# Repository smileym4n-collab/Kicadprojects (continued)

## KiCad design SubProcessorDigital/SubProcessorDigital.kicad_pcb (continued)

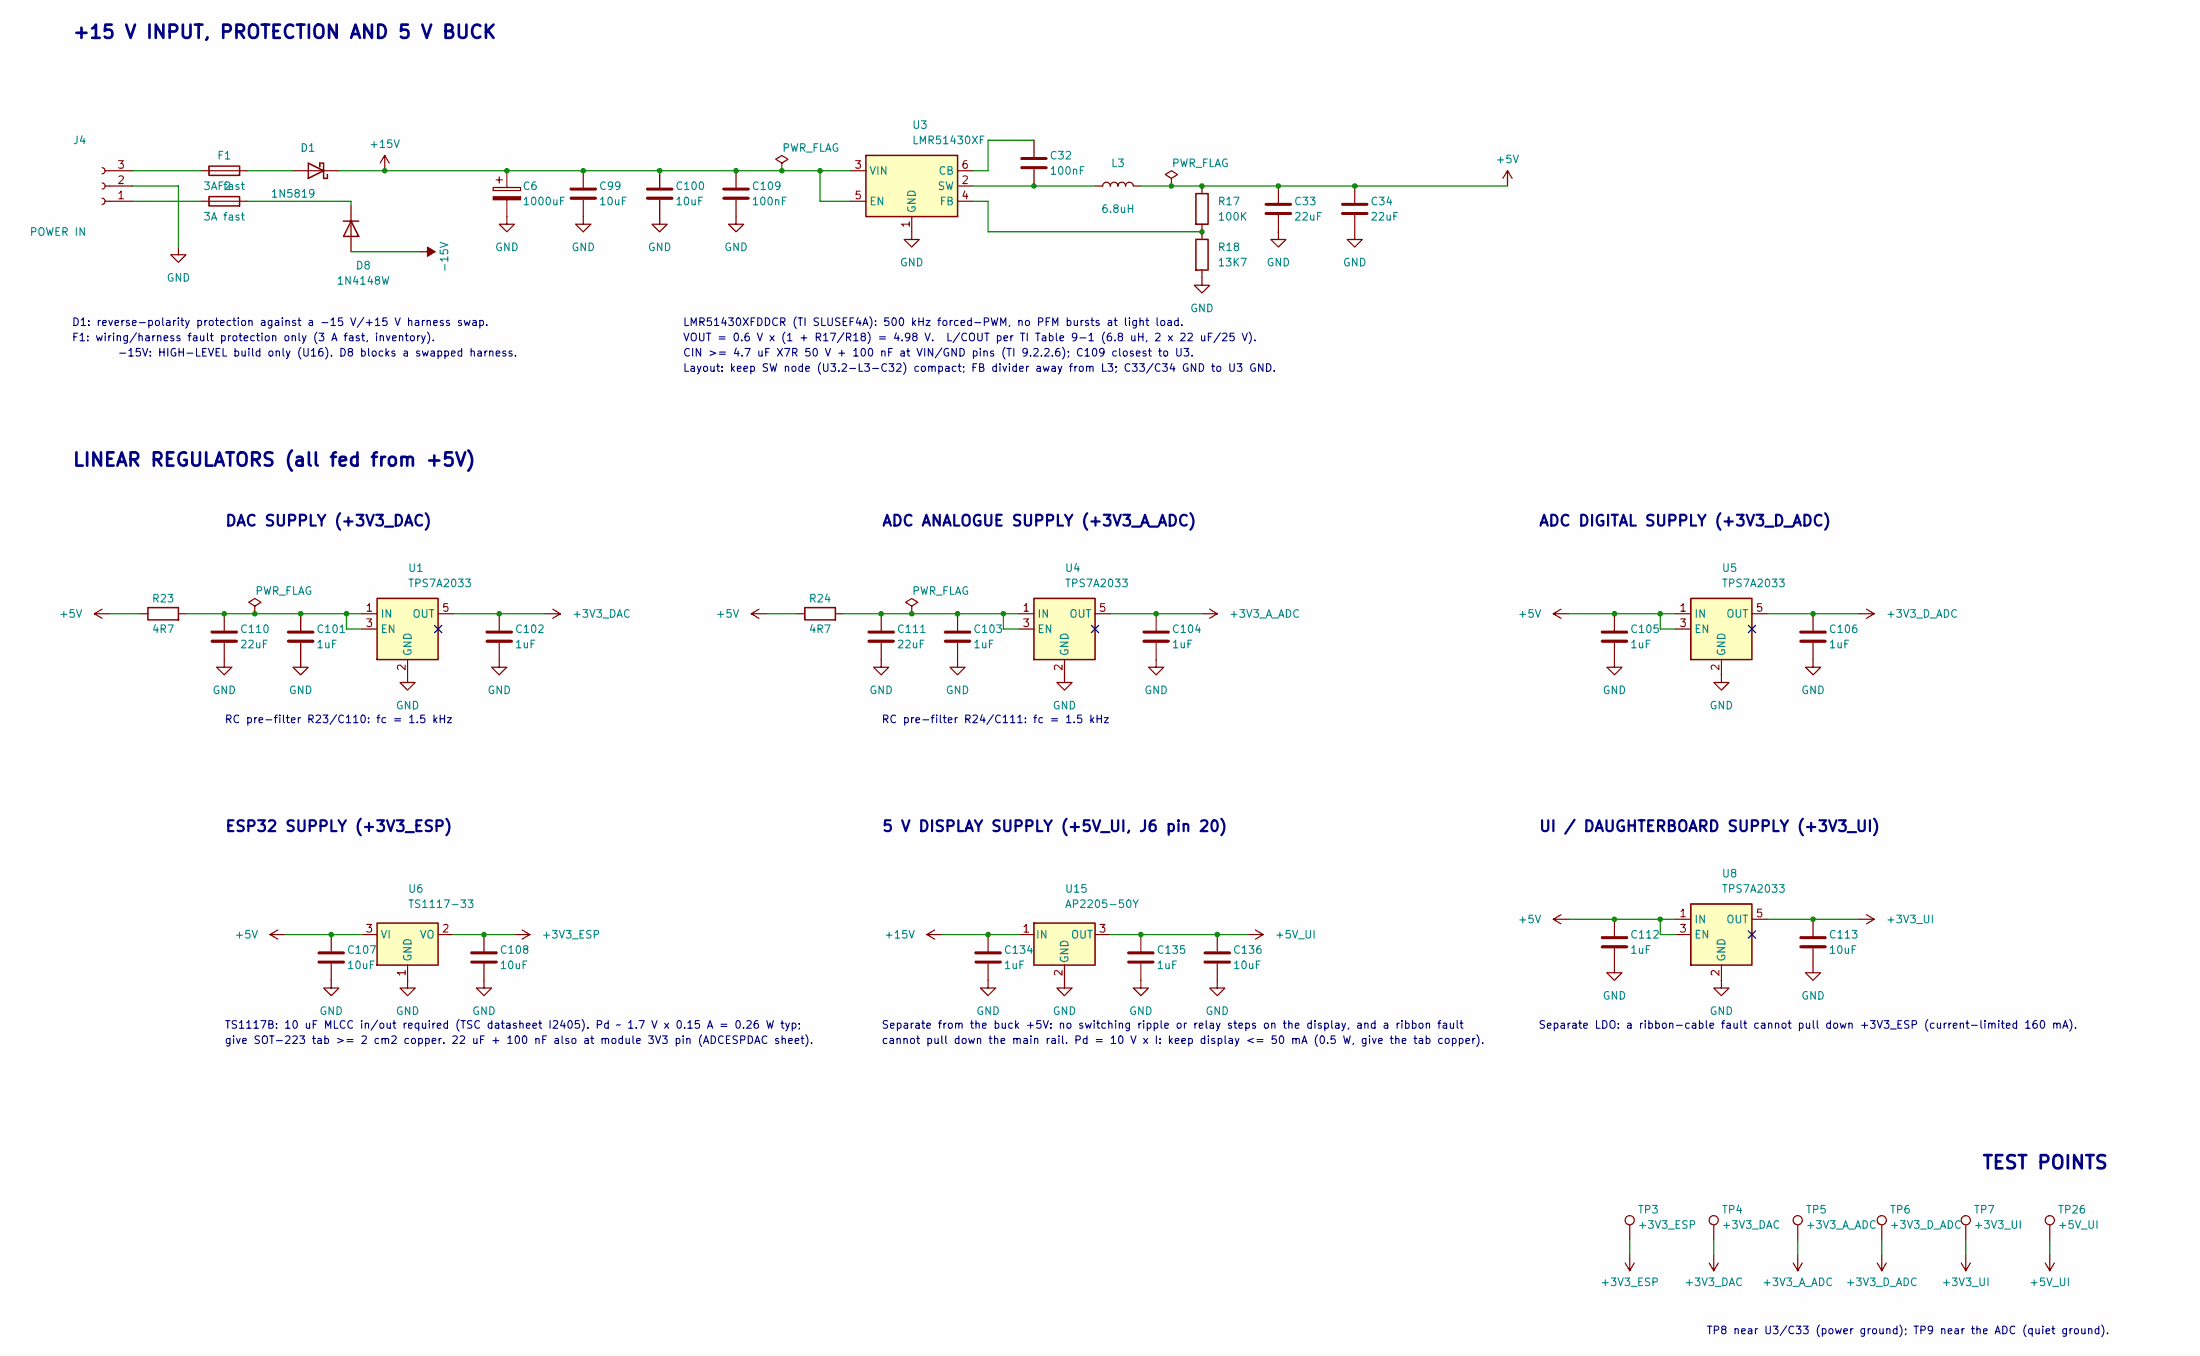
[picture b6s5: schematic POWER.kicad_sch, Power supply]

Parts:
C6: 1000uF; CP_Radial_D12.5mm_P5.00mm; MPN Panasonic EEUFR1V102 (FR)
C32, C109: 100nF; C_0603_1608Metric_Pad1.08x0.95mm_HandSolder; MPN Multicomp Pro MC0603B104K500CT (100nF 5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
C33, C34: 22uF; C_1206_3216Metric_Pad1.33x1.80mm_HandSolder; MPN Samsung CL31A226KAHNNNE X5R 25V 3216 (i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
C99, C100: 10uF; C_1206_3216Metric_Pad1.33x1.80mm_HandSolder; MPN Samsung CL31A106KBHNNNE (inventory)
C101, C102, C103, C104, C105, C106, C112: 1uF; C_1206_3216Metric_Pad1.33x1.80mm_HandSolder; MPN Samsung CL31B105KBHNFNE
C107, C108: 10uF; C_1206_3216Metric_Pad1.33x1.80mm_HandSolder; MPN Taiyo Yuden TMK316B7106KL-TD
C110, C111: 22uF; C_1206_3216Metric_Pad1.33x1.80mm_HandSolder; MPN Samsung CL31A226KAHNNNE (22uF 25V X5R 3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
C113: 10uF; C_0805_2012Metric_Pad1.18x1.45mm_HandSolder; MPN Samsung CL21A106KOQNNNF
C134, C135: 1uF; C_1206_3216Metric_Pad1.33x1.80mm_HandSolder; MPN Samsung CL31B105KBHNFNE (inventory)
C136: 10uF; C_0805_2012Metric_Pad1.18x1.45mm_HandSolder; MPN Samsung CL21A106KOQNNNF (inventory)
D1: 1N5819; D_DO-41_SOD81_P10.16mm_Horizontal; MPN Diotec 1N5819
D8: 1N4148W; D_SOD-123; MPN onsemi 1N4148W (inventory)
F1, F2: 3A fast; Fuse_1206_3216Metric_Pad1.42x1.75mm_HandSolder; MPN Bel Fuse C1F 3
J4: POWER IN; JST_XH_B3B-XH-A_1x03_P2.50mm_Vertical; MPN JST B3B-XH-A
L3: 6.8uH; SRP6030WA-6R8M; MPN Bourns SRP6030WA-6R8M (inventory)
R17: 100K; R_0805_2012Metric_Pad1.20x1.40mm_HandSolder; MPN 100k thin film 0.5% 2012 (inventory)
R18: 13K7; R_0805_2012Metric_Pad1.20x1.40mm_HandSolder; MPN 13k7 thick film 1% 2012 (inventory)
R23, R24: 4R7; R_0805_2012Metric_Pad1.20x1.40mm_HandSolder; MPN 4R7 thick film 2012 (inventory)
TP3: +3V3_ESP; TestPoint_Pad_D1.5mm
TP4: +3V3_DAC; TestPoint_Pad_D1.5mm
TP5: +3V3_A_ADC; TestPoint_Pad_D1.5mm
TP6: +3V3_D_ADC; TestPoint_Pad_D1.5mm
TP7: +3V3_UI; TestPoint_Pad_D1.5mm
TP26: +5V_UI; TestPoint_Pad_D1.5mm
U1, U4, U5, U8: TPS7A2033; SOT-23-5; MPN TPS7A2033PDBVR
U3: LMR51430XF; SOT-23-6; MPN LMR51430XFDDCR
U6: TS1117-33; SOT-223-3_TabPin2; MPN Taiwan Semiconductor TS1117BCW33 RPG
U15: AP2205-50Y; SOT-89-3; MPN Diodes Inc AP2205-50Y-13

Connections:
+3V3_A_ADC: C104.1, TP5.1 (1_1), U4.5 (OUT); also elsewhere on the board
+3V3_DAC: C102.1, TP4.1 (1_1), U1.5 (OUT); also elsewhere on the board
+3V3_D_ADC: C106.1, TP6.1 (1_1), U5.5 (OUT); also elsewhere on the board
+3V3_ESP: C108.1, TP3.1 (1_1), U6.2 (VO); also elsewhere on the board
+3V3_UI: C113.1, TP7.1 (1_1), U8.5 (OUT); also elsewhere on the board
+5V: C33.1, C34.1, C105.1, C107.1, C112.1, L3.2, R17.1, R23.1, R24.1, U5.1 (IN), U5.3 (EN), U6.3 (VI), U8.1 (IN), U8.3 (EN); also elsewhere on the board
+5V_UI: C135.1, C136.1, TP26.1 (1_1), U15.3 (OUT); also elsewhere on the board
+15V: C6.1, C99.1, C100.1, C109.1, C134.1, D1.1 (K), U3.3 (VIN), U3.5 (EN), U15.1 (IN); also elsewhere on the board
-15V: D8.2 (A); also elsewhere on the board
GND: C6.2, C33.2, C34.2, C99.2, C100.2, C101.2, C102.2, C103.2, C104.2, C105.2, C106.2, C107.2, C108.2, C109.2, C110.2, C111.2, C112.2, C113.2, C134.2, C135.2, C136.2, J4.2, R18.2, U1.2 (GND), U3.1 (GND), U4.2 (GND), U5.2 (GND), U6.1 (GND), U8.2 (GND), U15.2 (GND); also elsewhere on the board
unnamed: D1.2 (A), F1.2
unnamed: D8.1 (K), F2.2
unnamed: F2.1, J4.1
unnamed: F1.1, J4.3
unnamed: C101.1, C110.1, R23.2, U1.1 (IN), U1.3 (EN)
unnamed: C32.1, U3.6 (CB)
unnamed: R17.2, R18.1, U3.4 (FB)
unnamed: C32.2, L3.1, U3.2 (SW)
unnamed: C103.1, C111.1, R24.2, U4.1 (IN), U4.3 (EN)

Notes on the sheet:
ESP32 SUPPLY (+3V3_ESP)
TS1117B: 10 uF MLCC in/out required (TSC datasheet I2405). Pd ~ 1.7 V x 0.15 A = 0.26 W typ;
TEST POINTS
UI / DAUGHTERBOARD SUPPLY (+3V3_UI)
Separate LDO: a ribbon-cable fault cannot pull down +3V3_ESP (current-limited 160 mA).
5 V DISPLAY SUPPLY (+5V_UI, J6 pin 20)
RC pre-filter R23/C110: fc = 1.5 kHz
Separate from the buck +5V: no switching ripple or relay steps on the display, and a ribbon fault
-15V: HIGH-LEVEL build only (U16). D8 blocks a swapped harness.
ADC DIGITAL SUPPLY (+3V3_D_ADC)
F1: wiring/harness fault protection only (3 A fast, inventory).
TP8 near U3/C33 (power ground); TP9 near the ADC (quiet ground).
give SOT-223 tab >= 2 cm2 copper. 22 uF + 100 nF also at module 3V3 pin (ADCESPDAC sheet).
CIN >= 4.7 uF X7R 50 V + 100 nF at VIN/GND pins (TI 9.2.2.6); C109 closest to U3.
LMR51430XFDDCR (TI SLUSEF4A): 500 kHz forced-PWM, no PFM bursts at light load.
RC pre-filter R24/C111: fc = 1.5 kHz
DAC SUPPLY (+3V3_DAC)
ADC ANALOGUE SUPPLY (+3V3_A_ADC)
+15 V INPUT, PROTECTION AND 5 V BUCK
VOUT = 0.6 V x (1 + R17/R18) = 4.98 V. L/COUT per TI Table 9-1 (6.8 uH, 2 x 22 uF/25 V).
LINEAR REGULATORS (all fed from +5V)
Layout: keep SW node (U3.2-L3-C32) compact; FB divider away from L3; C33/C34 GND to U3 GND.
cannot pull down the main rail. Pd = 10 V x I: keep display <= 50 mA (0.5 W, give the tab copper).
D1: reverse-polarity protection against a -15 V/+15 V harness swap.

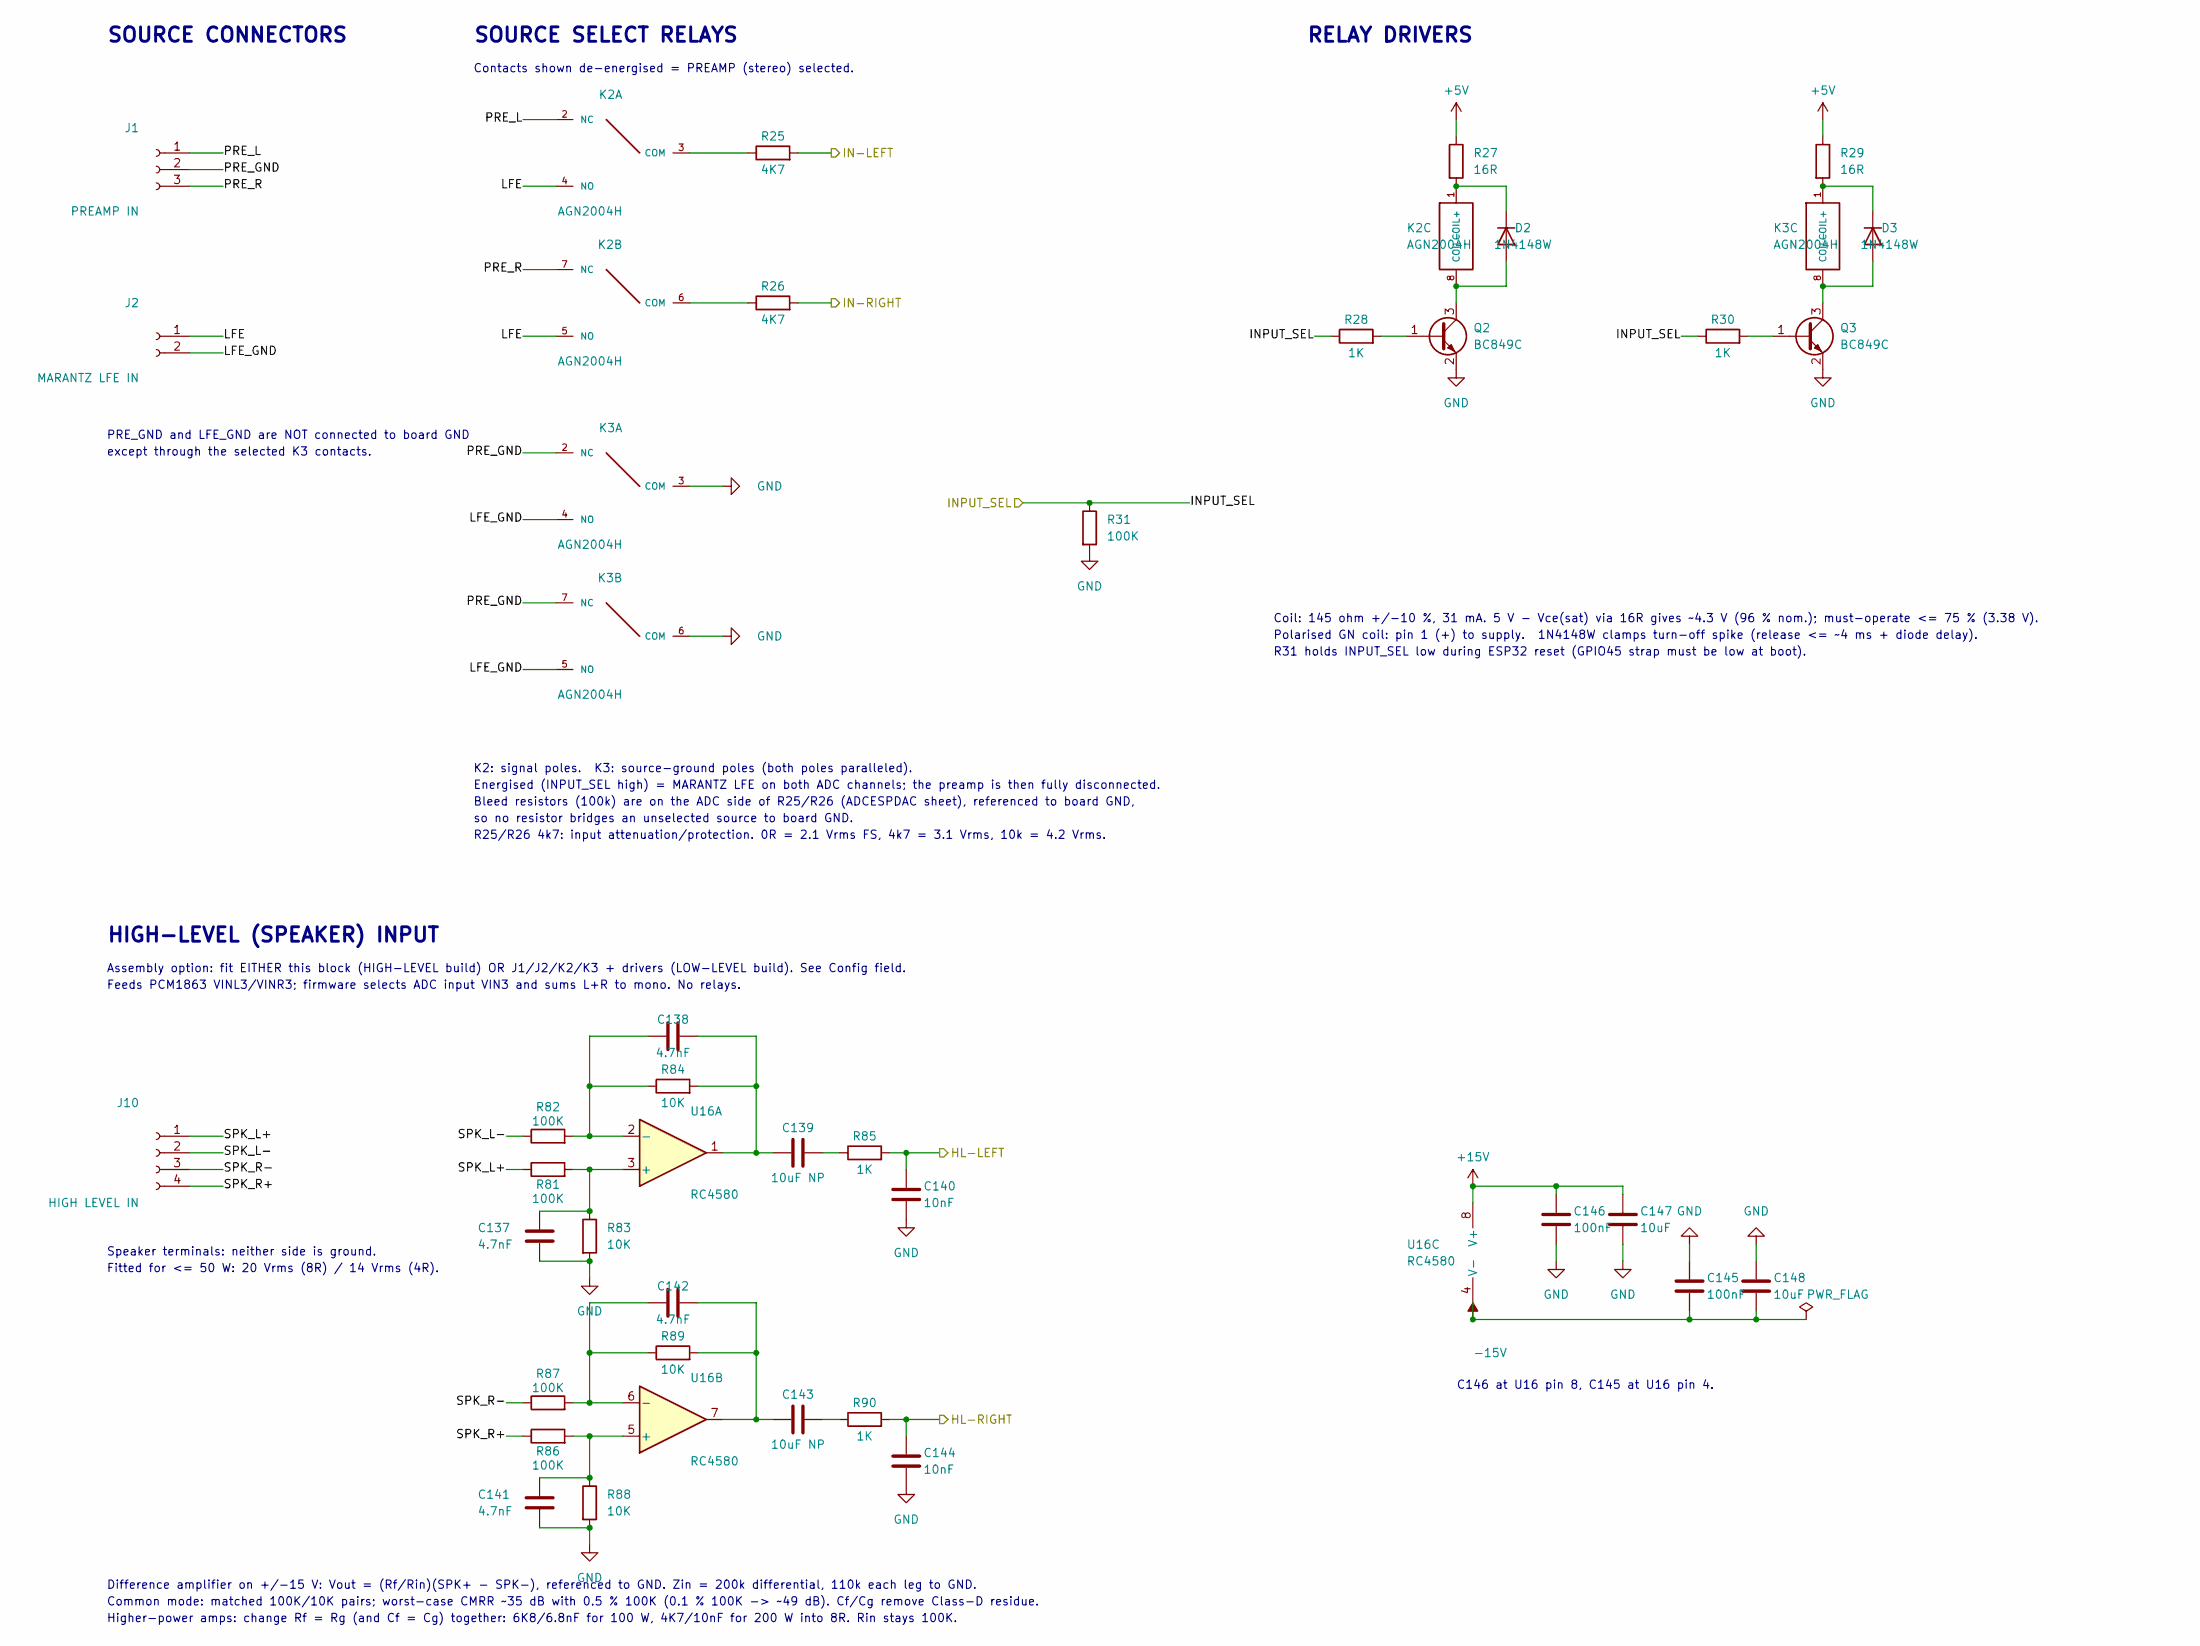
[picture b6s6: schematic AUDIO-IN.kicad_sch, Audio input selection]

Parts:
C137, C138, C141, C142: 4.7nF; C_0805_2012Metric_Pad1.18x1.45mm_HandSolder; MPN Walsin 0805N472J101CT C0G 100V (invento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
C139, C143: 10uF NP; C_Radial_D8.0mm_H11.5mm_P3.50mm; MPN Nichicon UES1H100MPM bipolar (inventory)
C140, C144: 10nF; C_0805_2012Metric_Pad1.18x1.45mm_HandSolder; MPN Walsin 0805N103J500CT C0G (inventory)
C145, C146: 100nF; C_0603_1608Metric_Pad1.08x0.95mm_HandSolder; MPN Multicomp Pro MC0603B104K500CT (100nF 5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
C147, C148: 10uF; C_1206_3216Metric_Pad1.33x1.80mm_HandSolder; MPN Taiyo Yuden TMK316B7106KL-TD 25V X7R (i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
D2, D3: 1N4148W; D_SOD-123; MPN onsemi 1N4148W (inventory)
J1: PREAMP IN; JST_XH_B3B-XH-A_1x03_P2.50mm_Vertical; MPN JST B3B-XH-A
J2: MARANTZ LFE IN; JST_XH_B2B-XH-A_1x02_P2.50mm_Vertical; MPN JST B2B-XH-A
J10: HIGH LEVEL IN; JST_XH_B4B-XH-A_1x04_P2.50mm_Vertical; MPN JST B4B-XH-A
K2, K3: AGN2004H; Relay_DPDT_Panasonic_AGN2004H; MPN Panasonic AGN2004H (inventory)
Q2, Q3: BC849C; SOT-23; MPN Nexperia BC849C,215 (purchase)
R25, R26: 4K7; R_0805_2012Metric_Pad1.20x1.40mm_HandSolder; MPN Yageo RT0805BRD074K7L thin film (invent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
R27, R29: 16R; R_0805_2012Metric_Pad1.20x1.40mm_HandSolder; MPN Stackpole RMCF0805FT16R0 (inventory)
R28, R30: 1K; R_0805_2012Metric_Pad1.20x1.40mm_HandSolder; MPN Thick film 2012 (inventory)
R31: 100K; R_0805_2012Metric_Pad1.20x1.40mm_HandSolder; MPN Thick film 2012 (inventory)
R81, R82, R86, R87: 100K; R_0805_2012Metric_Pad1.20x1.40mm_HandSolder; MPN 100K thin film 0.5% 2012 (inventory)
R83, R84, R88, R89: 10K; R_0805_2012Metric_Pad1.20x1.40mm_HandSolder; MPN 10K thin film 0.1% 2012 (inventory)
R85, R90: 1K; R_0805_2012Metric_Pad1.20x1.40mm_HandSolder; MPN 1K thin film 0.5% 2012 (inventory)
U16: RC4580; SOIC-8_3.9x4.9mm_P1.27mm; MPN Texas Instruments RC4580IDR SOIC-8 (inv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

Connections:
+5V: R27.1, R29.1; also elsewhere on the board
+15V: C146.1, C147.1, U16.8 (V+); also elsewhere on the board
-15V: C145.2, C148.2, U16.4 (V-); also elsewhere on the board
/AUDIO-IN/LFE: J2.1, K2.4 (NO), K2.5 (NO)
/AUDIO-IN/LFE_GND: J2.2, K3.4 (NO), K3.5 (NO)
/AUDIO-IN/PRE_GND: J1.2, K3.2 (NC), K3.7 (NC)
/AUDIO-IN/PRE_L: J1.1, K2.2 (NC)
/AUDIO-IN/PRE_R: J1.3, K2.7 (NC)
/AUDIO-IN/SPK_L+: J10.1, R81.1
/AUDIO-IN/SPK_L-: J10.2, R82.1
/AUDIO-IN/SPK_R+: J10.4, R86.1
/AUDIO-IN/SPK_R-: J10.3, R87.1
/HL-LEFT: C140.1, R85.2; also elsewhere on the board
/HL-RIGHT: C144.1, R90.2; also elsewhere on the board
/IN-LEFT: R25.2; also elsewhere on the board
/IN-RIGHT: R26.2; also elsewhere on the board
/INPUT_SEL: R28.1, R30.1, R31.1; also elsewhere on the board
GND: C137.2, C140.2, C141.2, C144.2, C145.1, C146.2, C147.2, C148.1, K3.3 (COM), K3.6 (COM), Q2.2 (E), Q3.2 (E), R31.2, R83.2, R88.2; also elsewhere on the board
unnamed: C138.2, C139.1, R84.2, U16.1
unnamed: C139.2, R85.1
unnamed: C142.2, C143.1, R89.2, U16.7
unnamed: C143.2, R90.1
unnamed: D2.2 (A), K2.8 (COIL-), Q2.3 (C)
unnamed: D2.1 (K), K2.1 (COIL+), R27.2
unnamed: D3.2 (A), K3.8 (COIL-), Q3.3 (C)
unnamed: D3.1 (K), K3.1 (COIL+), R29.2
unnamed: K2.3 (COM), R25.1
unnamed: K2.6 (COM), R26.1
unnamed: Q2.1 (B), R28.2
unnamed: Q3.1 (B), R30.2
unnamed: C137.1, R81.2, R83.1, U16.3 (+)
unnamed: C138.1, R82.2, R84.1, U16.2 (-)
unnamed: C141.1, R86.2, R88.1, U16.5 (+)
unnamed: C142.1, R87.2, R89.1, U16.6 (-)

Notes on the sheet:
Feeds PCM1863 VINL3/VINR3; firmware selects ADC input VIN3 and sums L+R to mono. No relays.
R25/R26 4k7: input attenuation/protection. 0R = 2.1 Vrms FS, 4k7 = 3.1 Vrms, 10k = 4.2 Vrms.
Polarised GN coil: pin 1 (+) to supply. 1N4148W clamps turn-off spike (release <= ~4 ms + diode delay).
Fitted for <= 50 W: 20 Vrms (8R) / 14 Vrms (4R).
SOURCE CONNECTORS
Speaker terminals: neither side is ground.
R31 holds INPUT_SEL low during ESP32 reset (GPIO45 strap must be low at boot).
K2: signal poles. K3: source-ground poles (both poles paralleled).
HIGH-LEVEL (SPEAKER) INPUT
except through the selected K3 contacts.
Energised (INPUT_SEL high) = MARANTZ LFE on both ADC channels; the preamp is then fully disconnected.
Contacts shown de-energised = PREAMP (stereo) selected.
PRE_GND and LFE_GND are NOT connected to board GND
so no resistor bridges an unselected source to board GND.
RELAY DRIVERS
Higher-power amps: change Rf = Rg (and Cf = Cg) together: 6K8/6.8nF for 100 W, 4K7/10nF for 200 W into 8R. Rin stays 100K.
Common mode: matched 100K/10K pairs; worst-case CMRR ~35 dB with 0.5 % 100K (0.1 % 100K -> ~49 dB). Cf/Cg remove Class-D residue.
Assembly option: fit EITHER this block (HIGH-LEVEL build) OR J1/J2/K2/K3 + drivers (LOW-LEVEL build). See Config field.
Difference amplifier on +/-15 V: Vout = (Rf/Rin)(SPK+ - SPK-), referenced to GND. Zin = 200k differential, 110k each leg to GND.
Coil: 145 ohm +/-10 %, 31 mA. 5 V - Vce(sat) via 16R gives ~4.3 V (96 % nom.); must-operate <= 75 % (3.38 V).
SOURCE SELECT RELAYS
Bleed resistors (100k) are on the ADC side of R25/R26 (ADCESPDAC sheet), referenced to board GND,
C146 at U16 pin 8, C145 at U16 pin 4.

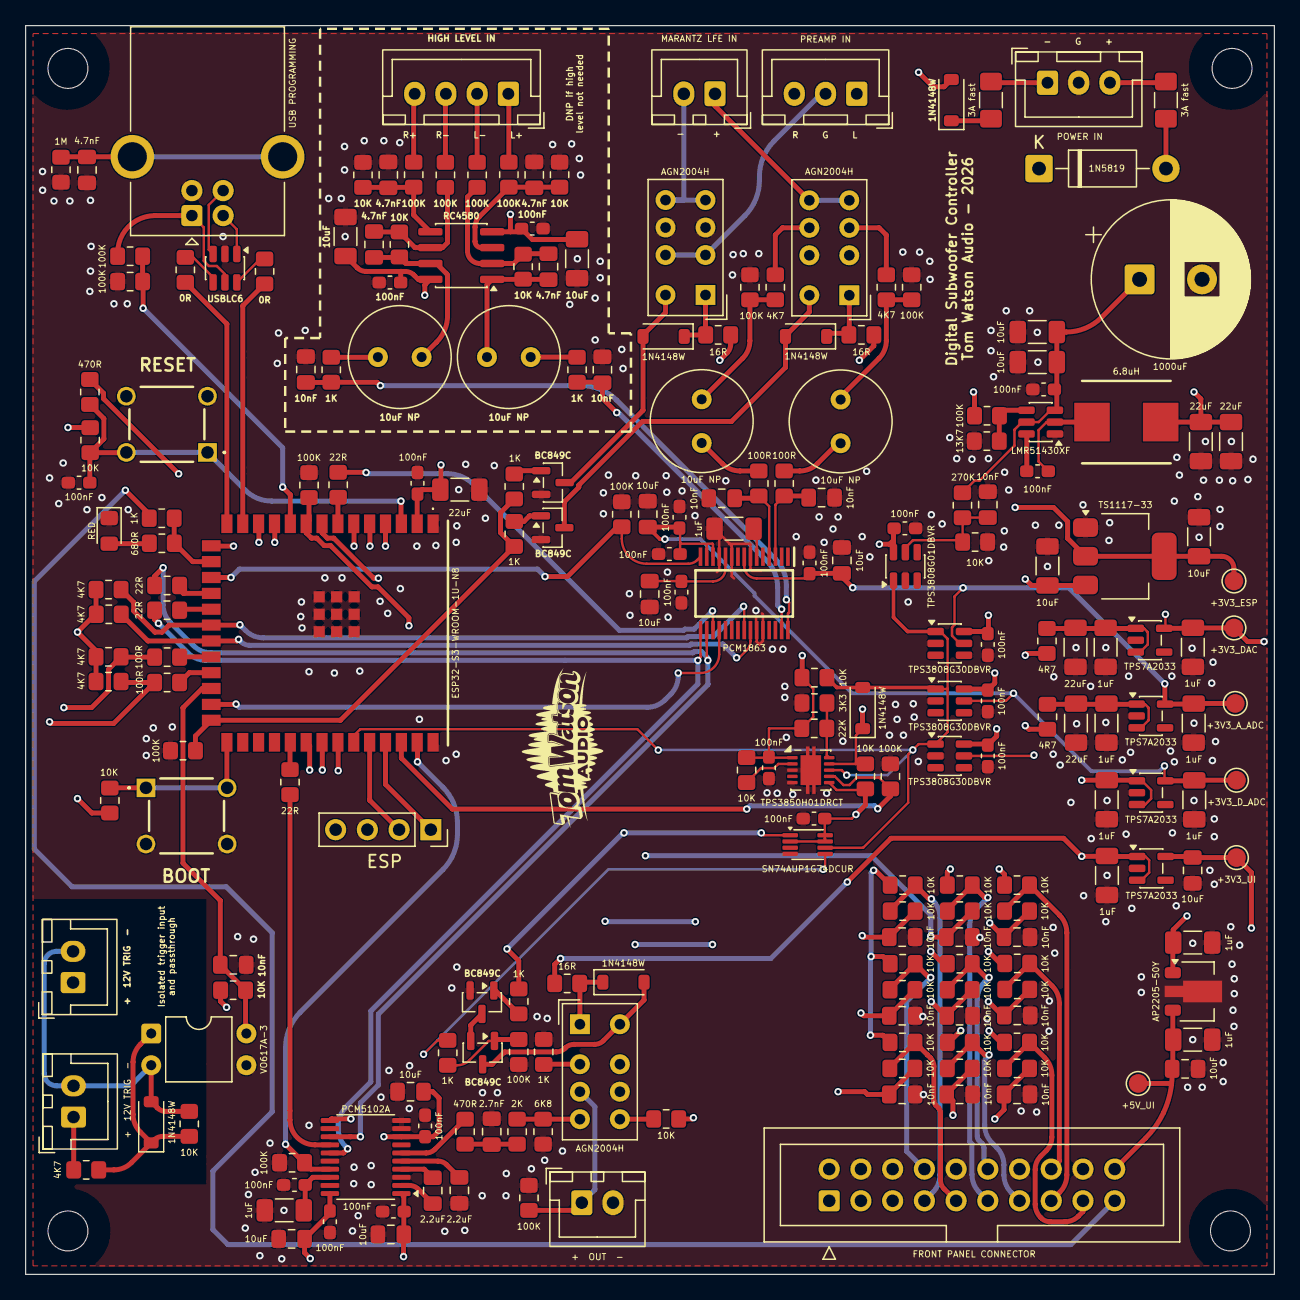
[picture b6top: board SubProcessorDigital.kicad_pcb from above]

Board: 4 copper layers, 100.0 x 100.0 mm, 224 parts (0 on the bottom side), 133 nets.

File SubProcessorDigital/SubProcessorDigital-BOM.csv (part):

"Refs","Value","Footprint","MPN","Notes","Config","Qty","DNP"
"C1,C2","10uF NP","Capacitor_THT:C_Radial_D8.0mm_H11.5mm_P3.50mm","Nichicon UES1H100MPM bipolar (inventory)","AC coupling; ADC input biased at AVDD/2","LOW-LEVEL build only","2",""
"C3,C4","10nF","Capacitor_SMD:C_0805_2012Metric_Pad1.18x1.45mm_HandSolder","Walsin 0805N103J500CT C0G (inventory)","","LOW-LEVEL build only","2",""
"C5,C8,C23,C32,C66-C68,C70,C71,C74,C75,C109,C114,C118,C120-C123","100nF","Capacitor_SMD:C_0603_1608Metric_Pad1.08x0.95mm_HandSolder","Multicomp Pro MC0603B104K500CT (100nF 50V X7R 10% 1608)","At U7 VDD,Reduced from 1uF: supervisor provides reset timing","","18",""
"C6","1000uF","Capacitor_THT:CP_Radial_D12.5mm_P5.00mm","Panasonic EEUFR1V102 (FR)","Inventory","","1",""
"C18,C20","2.2uF","Capacitor_SMD:C_0805_2012Metric_Pad1.18x1.45mm_HandSolder","Samsung CL21B225KPFNNNE X7R (inventory)","","","2",""
"C19,C24,C134,C135","1uF","Capacitor_SMD:C_1206_3216Metric_Pad1.33x1.80mm_HandSolder","Samsung CL31B105KBHNFNE (inventory)","VREF: 1 uF per SLAS831D","","4",""
"C21,C136","10uF","Capacitor_SMD:C_0805_2012Metric_Pad1.18x1.45mm_HandSolder","Samsung CL21A106KOQNNNF (inventory)","","","2",""
"C25","2.7nF","Capacitor_SMD:C_0805_2012Metric_Pad1.18x1.45mm_HandSolder","Walsin 0805N272J500CT C0G (inventory)","fc = 125 kHz with R13","","1",""
"C33,C34","22uF","Capacitor_SMD:C_1206_3216Metric_Pad1.33x1.80mm_HandSolder","Samsung CL31A226KAHNNNE X5R 25V 3216 (inventory)","","","2",""
"C69,C72,C76,C115,C116","10uF","Capacitor_SMD:C_0805_2012Metric_Pad1.18x1.45mm_HandSolder","Samsung CL21A106KOQNNNF X5R 16V (inventory)","","","5",""
"C77","22uF","Capacitor_SMD:C_1206_3216Metric_Pad1.33x1.80mm_HandSolder","Samsung CL31A226KAHNNNE X5R 25V (inventory)","","","1",""
"C99,C100","10uF","Capacitor_SMD:C_1206_3216Metric_Pad1.33x1.80mm_HandSolder","Samsung CL31A106KBHNNNE (inventory)","","","2",""
"C101-C106,C112","1uF","Capacitor_SMD:C_1206_3216Metric_Pad1.33x1.80mm_HandSolder","Samsung CL31B105KBHNFNE","","","7",""
"C107,C108","10uF","Capacitor_SMD:C_1206_3216Metric_Pad1.33x1.80mm_HandSolder","Taiyo Yuden TMK316B7106KL-TD","","","2",""
"C110,C111","22uF","Capacitor_SMD:C_1206_3216Metric_Pad1.33x1.80mm_HandSolder","Samsung CL31A226KAHNNNE (22uF 25V X5R 3216, inventory)","","","2",""
"C113","10uF","Capacitor_SMD:C_0805_2012Metric_Pad1.18x1.45mm_HandSolder","Samsung CL21A106KOQNNNF","","","1",""
"C117","4.7nF","Capacitor_SMD:C_0805_2012Metric_Pad1.18x1.45mm_HandSolder","Walsin 0805N472J101CT C0G 100V (inventory)","","","1",""
"C119","10nF","Capacitor_SMD:C_0805_2012Metric_Pad1.18x1.45mm_HandSolder","Walsin 0805B103K500CT (inventory)","Noise filter, tau ~ 0.1 ms","","1",""
"C124-C133","10nF","Capacitor_SMD:C_0805_2012Metric_Pad1.18x1.45mm_HandSolder","Walsin 0805N103J500CT (inventory)","","","10",""
"C137,C138,C141,C142","4.7nF","Capacitor_SMD:C_0805_2012Metric_Pad1.18x1.45mm_HandSolder","Walsin 0805N472J101CT C0G 100V (inventory)","Must match Cg: fc = 3.4 kHz","HIGH-LEVEL build only","4",""
"C139,C143","10uF NP","Capacitor_THT:C_Radial_D8.0mm_H11.5mm_P3.50mm","Nichicon UES1H100MPM bipolar (inventory)","DC block: ADC input is self-biased at AVDD/2","HIGH-LEVEL build only","2",""
"C140,C144","10nF","Capacitor_SMD:C_0805_2012Metric_Pad1.18x1.45mm_HandSolder","Walsin 0805N103J500CT C0G (inventory)","Place at PCM1863 pin","HIGH-LEVEL build only","2",""
"C145,C146","100nF","Capacitor_SMD:C_0603_1608Metric_Pad1.08x0.95mm_HandSolder","Multicomp Pro MC0603B104K500CT (100nF 50V X7R 10% 1608)","","HIGH-LEVEL build only","2",""
"C147,C148","10uF","Capacitor_SMD:C_1206_3216Metric_Pad1.33x1.80mm_HandSolder","Taiyo Yuden TMK316B7106KL-TD 25V X7R (inventory)","","HIGH-LEVEL build only","2",""
"D1","1N5819","Diode_THT:D_DO-41_SOD81_P10.16mm_Horizontal","Diotec 1N5819","Reverse-polarity protection; inventory","","1",""
"D2,D3","1N4148W","Diode_SMD:D_SOD-123","onsemi 1N4148W (inventory)","","LOW-LEVEL build only","2",""
"D4,D5,D7","1N4148W","Diode_SMD:D_SOD-123","onsemi 1N4148W (inventory)","Reverse-polarity clamp for opto LED (VR max 6 V),Supply reset also clears the latch (FAULT_N low ~0.6 V < VIL 0.9 V)","","3",""
"D6","RED","LED_SMD:LED_0805_2012Metric_Pad1.15x1.40mm_HandSolder","Kingbright KP-2012EC (inventory)","","","1",""
"D8","1N4148W","Diode_SMD:D_SOD-123","onsemi 1N4148W (inventory)","Reverse protection: blocks +15V if the J4 harness is swapped","HIGH-LEVEL build only","1",""
"F1,F2","3A fast","Fuse:Fuse_1206_3216Metric_Pad1.42x1.75mm_HandSolder","Bel Fuse C1F 3","Inventory","","2",""
"H1-H4","M3","MountingHole:MountingHole_3.2mm_M3","","","","4",""
"IC1","ESP32-S3-WROOM-1U-N8","SPD:ESP32S3WROOM1UN16R8","ESP32-S3-WROOM-1U-N8","Inventory. Footprint common to all WROOM-1U variants. No antenna needed (RF unused).","","1",""
"IC2","PCM1863","SPD:SOP50P640X120-30N","PCM1863QDBTRQ1 (or PCM1863DBTR)","","","1",""
"IC3","USBLC6","Package_TO_SOT_SMD:SOT-23-6","STMicroelectronics USBLC6-2SC6 (inventory)","","","1",""
"IC4","RESET","SPD:TS026650BK100SCRD","Same Sky TS02-66-50-BK-100-SCR-D (inventory)","","","1",""
"IC5","BOOT","SPD:TS026650BK100SCRD","Same Sky TS02-66-50-BK-100-SCR-D (inventory)","","","1",""
"J1","PREAMP IN","Connector_JST:JST_XH_B3B-XH-A_1x03_P2.50mm_Vertical","JST B3B-XH-A","1 = L, 2 = preamp GND, 3 = R","LOW-LEVEL build only","1",""
"J2","MARANTZ LFE IN","Connector_JST:JST_XH_B2B-XH-A_1x02_P2.50mm_Vertical","JST B2B-XH-A","1 = LFE, 2 = Marantz GND","LOW-LEVEL build only","1",""
"J3","USB PROGRAMMING","Connector_USB:USB_B_OST_USB-B1HSxx_Horizontal","On Shore USB-B1HSW6 (check vs. stocked USB-B part)","","","1",""
"J4","POWER IN","Connector_JST:JST_XH_B3B-XH-A_1x03_P2.50mm_Vertical","JST B3B-XH-A","Pin3 +15V, Pin2 GND, Pin1 -15V (used by HIGH-LEVEL input op-amp U16)","","1",""
"J5","+  OUT  -","Connector_JST:JST_XH_B2B-XH-A_1x02_P2.50mm_Vertical","JST B2B-XH-A","1 = signal, 2 = GND","","1",""
"J6","FRONT PANEL CONNECTOR","Connector_IDC:IDC-Header_2x10_P2.54mm_Vertical","Shrouded box header 2x10 2.54 mm, e.g. Wurth 61202021621","Replaces DIN41612 symbol (pin names did not match IDC footprint)","","1",""
"J7,J9","+  12V TRIG  -","Connector_JST:JST_XH_B2B-XH-A_1x02_P2.50mm_Vertical","JST B2B-XH-A","1 = +12 V trigger, 2 = trigger return (isolated)","","2",""
"J8","UART0","Connector_PinHeader_2.54mm:PinHeader_1x03_P2.54mm_Vertical","2.54 mm 1x3 pin header","","","1",""
"J10","HIGH LEVEL IN","Connector_JST:JST_XH_B4B-XH-A_1x04_P2.50mm_Vertical","JST B4B-XH-A","1 = L+, 2 = L-, 3 = R-, 4 = R+. NO terminal is ground (BTL amps).","HIGH-LEVEL build only","1",""
"K1","AGN2004H","SPD:Relay_DPDT_Panasonic_AGN2004H","Panasonic AGN2004H (inventory)","","","1",""
"K2,K3","AGN2004H","SPD:Relay_DPDT_Panasonic_AGN2004H","Panasonic AGN2004H (inventory)","","LOW-LEVEL build only","2",""
"L3","6.8uH","SPD:SRP6030WA-6R8M","Bourns SRP6030WA-6R8M (inventory)","Isat 6.1 A, Irms 5.2 A, DCR 42 mohm","","1",""
"Q1,Q4","BC849C","Package_TO_SOT_SMD:SOT-23","Nexperia BC849C,215 (purchase)","Lower switch: AUDIO_READY,Upper switch: latch Q","","2",""
"Q2,Q3","BC849C","Package_TO_SOT_SMD:SOT-23","Nexperia BC849C,215 (purchase)","","LOW-LEVEL build only","2",""
"R1,R2,R56,R57","4K7","Resistor_SMD:R_0805_2012Metric_Pad1.20x1.40mm_HandSolder","Stackpole RMCF0805FT4K70 (inventory)","","","4",""
"R3,R4","100R","Resistor_SMD:R_0805_2012Metric_Pad1.20x1.40mm_HandSolder","100R thin film 2012 (inventory)","TI SLAS831D Fig 61","LOW-LEVEL build only","2",""
"R5,R6,R10,R11,R41,R58-R75,R79,R80","10K","Resistor_SMD:R_0805_2012Metric_Pad1.20x1.40mm_HandSolder","KOA RK73B2ATTD103J (inventory)","LED shunt: ignores < ~1.5 V / leakage","","25",""
"R7,R8","100K","Resistor_SMD:R_0805_2012Metric_Pad1.20x1.40mm_HandSolder","100k thin film 2012 (inventory)","Bleed: holds relay COM side at 0 V","LOW-LEVEL build only","2",""
"R9,R52","10K","Resistor_SMD:R_0805_2012Metric_Pad1.20x1.40mm_HandSolder","10k 0.1% thin film 2012 (inventory)","CWD to VDD (9-11k): factory timing","","2",""
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
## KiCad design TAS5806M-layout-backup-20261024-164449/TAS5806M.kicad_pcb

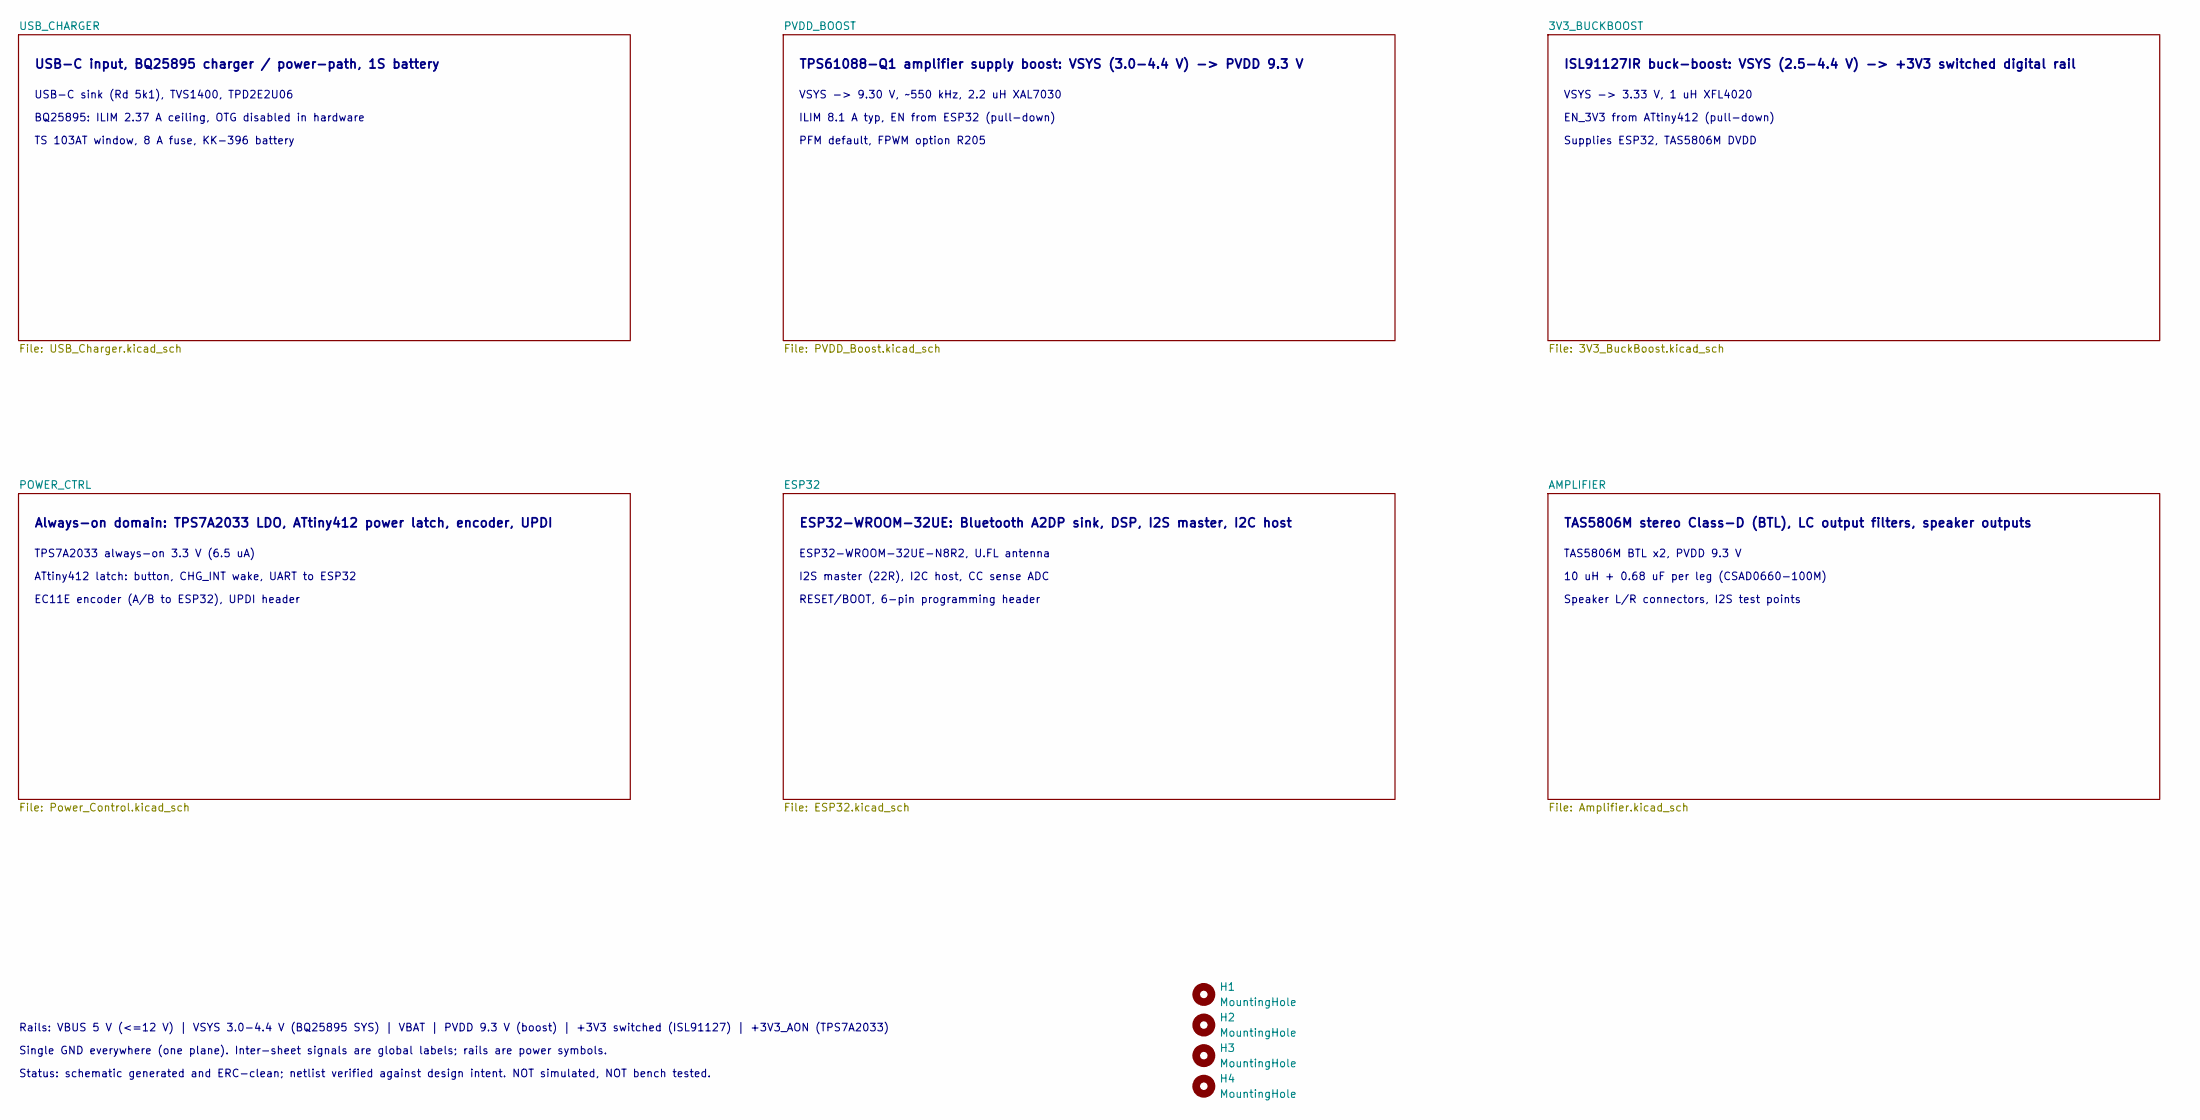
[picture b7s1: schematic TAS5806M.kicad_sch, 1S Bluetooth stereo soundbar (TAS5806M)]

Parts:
H1, H2, H3, H4: MountingHole; MountingHole_3.2mm_M3

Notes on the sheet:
RESET/BOOT, 6-pin programming header
TS 103AT window, 8 A fuse, KK-396 battery
EN_3V3 from ATtiny412 (pull-down)
ESP32-WROOM-32UE-N8R2, U.FL antenna
EC11E encoder (A/B to ESP32), UPDI header
Single GND everywhere (one plane). Inter-sheet signals are global labels; rails are power symbols.
PFM default, FPWM option R205
Rails: VBUS 5 V (<=12 V) | VSYS 3.0-4.4 V (BQ25895 SYS) | VBAT | PVDD 9.3 V (boost) | +3V3 switched (ISL91127) | +3V3_AON (TPS7A2033)
ILIM 8.1 A typ, EN from ESP32 (pull-down)
10 uH + 0.68 uF per leg (CSAD0660-100M)
USB-C sink (Rd 5k1), TVS1400, TPD2E2U06
USB-C input, BQ25895 charger / power-path, 1S battery
Speaker L/R connectors, I2S test points
I2S master (22R), I2C host, CC sense ADC
TAS5806M stereo Class-D (BTL), LC output filters, speaker outputs
BQ25895: ILIM 2.37 A ceiling, OTG disabled in hardware
TPS61088-Q1 amplifier supply boost: VSYS (3.0-4.4 V) -> PVDD 9.3 V
VSYS -> 3.33 V, 1 uH XFL4020
TPS7A2033 always-on 3.3 V (6.5 uA)
Always-on domain: TPS7A2033 LDO, ATtiny412 power latch, encoder, UPDI
ISL91127IR buck-boost: VSYS (2.5-4.4 V) -> +3V3 switched digital rail
Supplies ESP32, TAS5806M DVDD
TAS5806M BTL x2, PVDD 9.3 V
ESP32-WROOM-32UE: Bluetooth A2DP sink, DSP, I2S master, I2C host
Status: schematic generated and ERC-clean; netlist verified against design intent. NOT simulated, NOT bench tested.
VSYS -> 9.30 V, ~550 kHz, 2.2 uH XAL7030
ATtiny412 latch: button, CHG_INT wake, UART to ESP32
